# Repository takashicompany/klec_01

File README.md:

# KLEC-01 "Filled46"

https://x.com/takashicompany/status/1845085013051834711

# 部品リスト

|画像|部品名|個数|備考|
|:--|:--|:--|:--|
||KLEC-01 PCB|1|ガーバデータは[こちら](https://github.com/takashicompany/klec_01/tree/master/gerber)にあります。Kicadのプロジェクトは[こちら](https://github.com/takashicompany/klec_01/tree/master/kicad)です。|
||[Pro Micro](https://shop.yushakobo.jp/products/21)|1|どれを買っていいか分からない場合は[コンスルー付きのセット](https://shop.yushakobo.jp/products/21)の購入を推奨します。|
||[タクトスイッチ](https://shop.yushakobo.jp/products/a0800ts-01-1)|1||
||[コンスルー](https://shop.yushakobo.jp/products/31)|2|PCBとPro Microを接続する端子です。Pro Microに付属するピンヘッダでの取り付けも可能ですが、作業ミスや故障した際の取り替えが容易になりますので、**コンスルーの使用を強く推奨します。ピンヘッダでの取り付けは当キーボードと当ビルドガイドではサポートしません。** コンスルーの必要な高さはPro Microによって異なりますので、販売元にご確認ください。コンスルーについての詳細な説明は[こちら](https://scrapbox.io/self-made-kbds-ja/%E3%82%B3%E3%83%B3%E3%82%B9%E3%83%AB%E3%83%BC)をご一読ください。併せて[取り付け方の説明](https://yushakobo.zendesk.com/hc/ja/articles/360044233974-%E3%82%B3%E3%83%B3%E3%82%B9%E3%83%AB%E3%83%BC-%E3%82%B9%E3%83%97%E3%83%AA%E3%83%B3%E3%82%B0%E3%83%94%E3%83%B3%E3%83%98%E3%83%83%E3%83%80-%E3%81%AE%E5%8F%96%E3%82%8A%E4%BB%98%E3%81%91%E6%96%B9%E3%82%92%E6%95%99%E3%81%88%E3%81%A6%E4%B8%8B%E3%81%95%E3%81%84)も目を通しておくと作業がスムーズに進められます。|
||[MX互換キースイッチ](https://shop.yushakobo.jp/collections/all-switches)|46||
||[MX互換キーキャップ](https://shop.yushakobo.jp/collections/keycaps)|46|[こちら](https://www.keyboard-layout-editor.com/#/gists/d532e57cda0be36ffc0e33e7f8f69d8d)から各キーのサイズを確認できます。|
||[スタビライザー](https://shop.yushakobo.jp/products/a0500st)|2|
||[ウレタンクッション](https://shop.yushakobo.jp/products/a0800ur-01-6)|6|数はお好みで増減させてください。|
||アクリルケース|1|[こちらのデータ](https://github.com/takashicompany/klec_01/blob/master/case/klec_01_a4_yushakobo.ai)を遊舎工房の[レーザー加工サービス](https://shop.yushakobo.jp/products/lasercut?variant=48787700744423)にてカット依頼するなどして製造してください。後日に[キーボードアクリルプレート](https://shop.yushakobo.jp/products/keyboard_acrylic_plate)に追加予定です。|
||[M2スペーサー](https://shop.yushakobo.jp/products/a0800c2?variant=37665435222177)|8|長さはお好みで調整してください。Pro Microなどにもよりますが、7mm~10mmぐらいがオススメです。|
||[M2ネジ 5mm](https://shop.yushakobo.jp/products/a0800n2?variant=37665432993953)|16||

# ファームウェア

QMK Firmwareで用意しています。
ソースコードは[こちら](https://github.com/takashicompany/qmk_firmware/tree/master/keyboards/takashicompany/klec_01)です。

RemapにVIAファームウェアを登録しておりますので、[こちら](https://remap-keys.app/catalog/Tp7FO3o6xTwo2X9V9IJW/firmware)から書き込みが可能です。
キーマップの変更も[Remap](https://remap-keys.app/)から可能です。

# LICENSE

CC BY-NC 4.0

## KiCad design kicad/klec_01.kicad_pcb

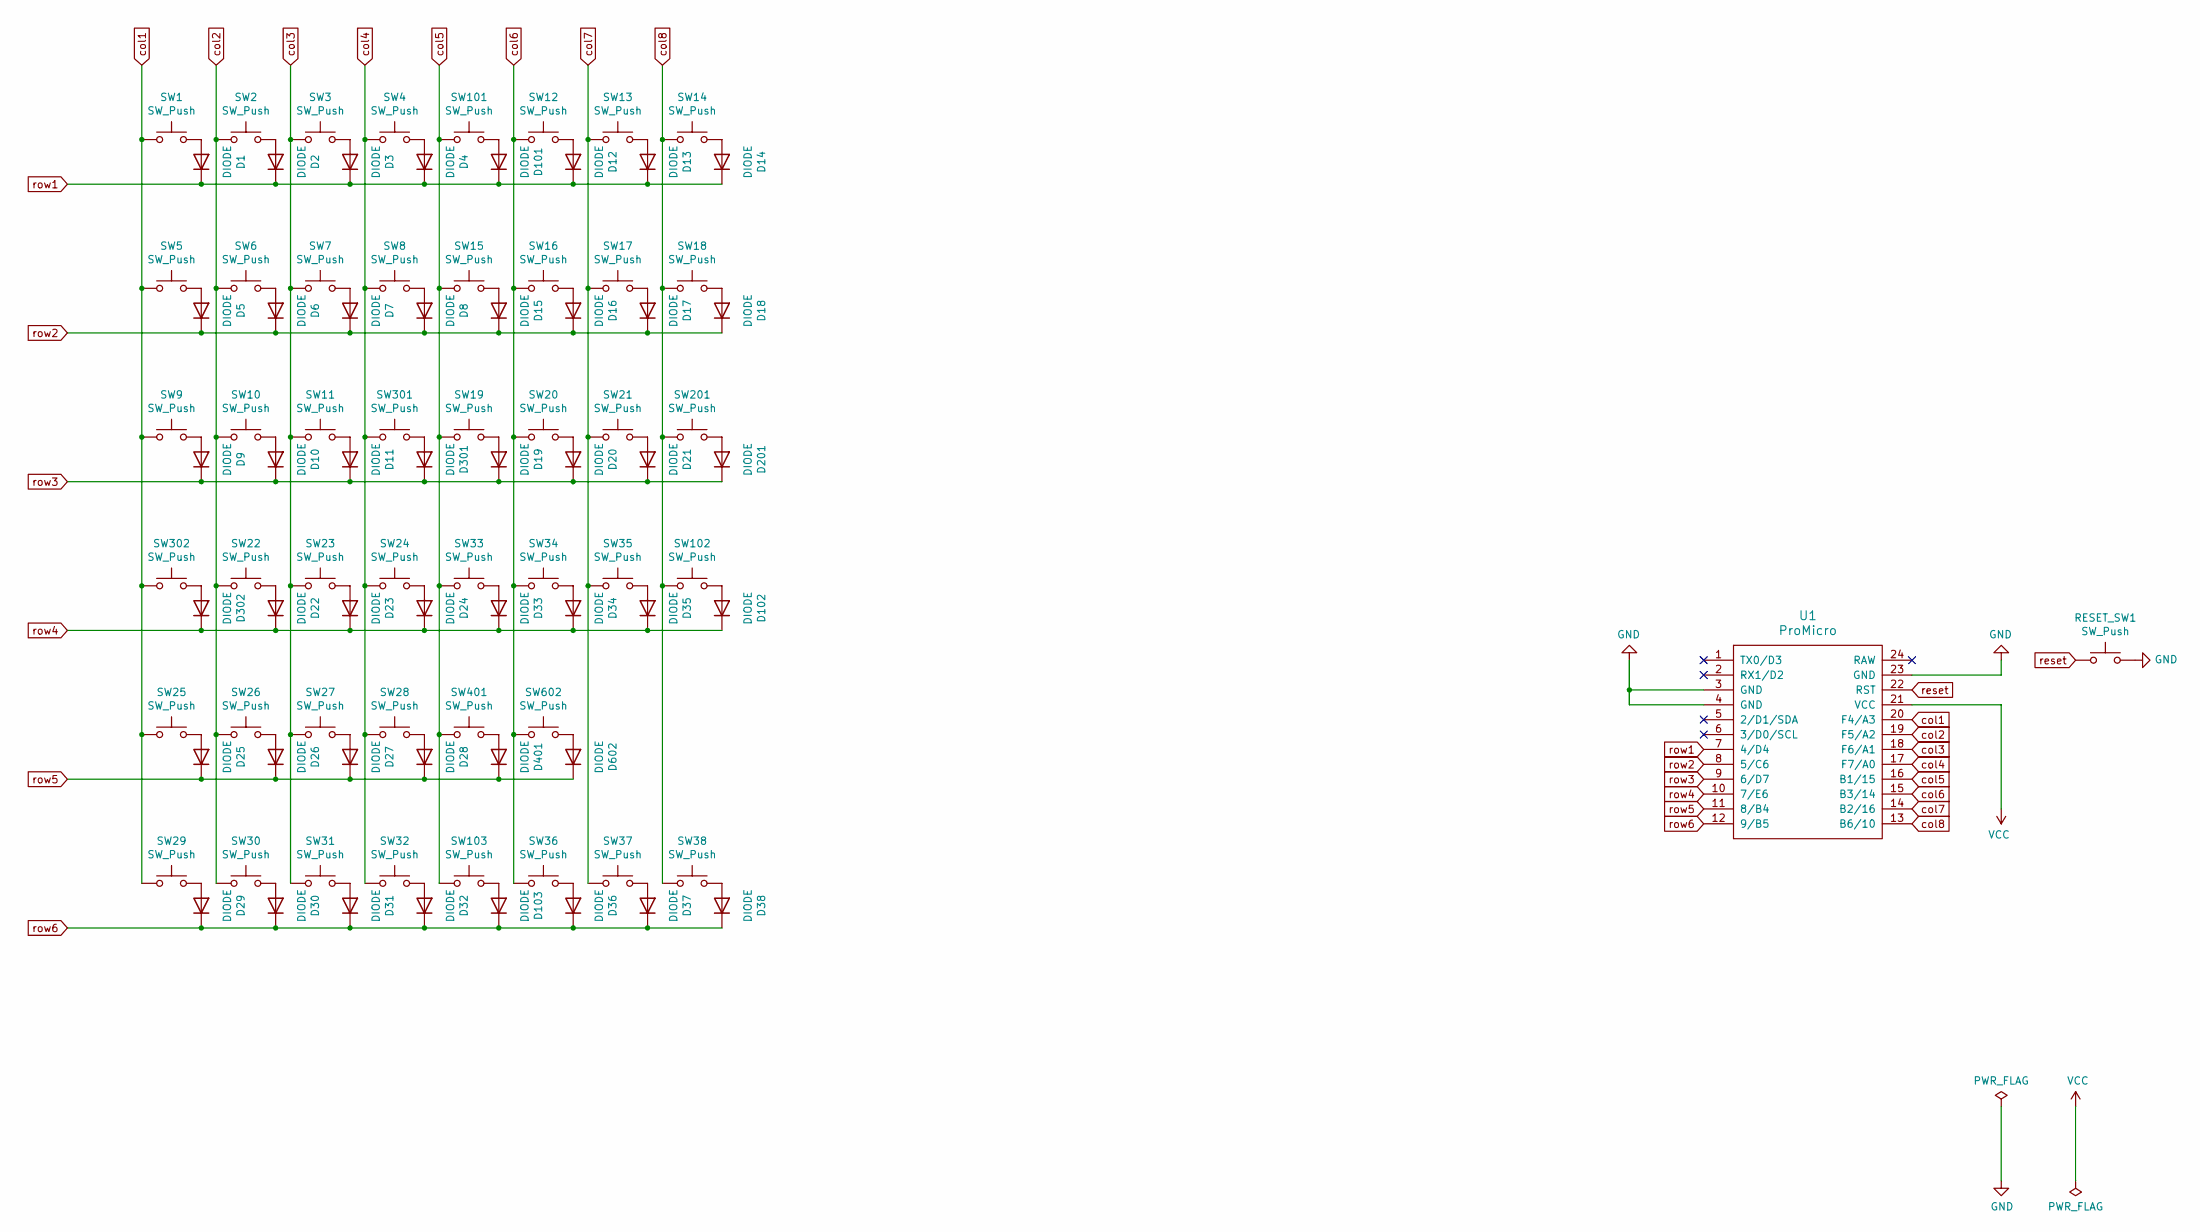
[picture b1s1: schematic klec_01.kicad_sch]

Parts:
D1, D2, D3, D4, D5, D6, D7, D8, D9, D10, D11, D12, D13, D14, D15, D16, D17, D18, D19, D20, D21, D22, D23, D24, D25, D26, D27, D28, D29, D30, D31, D32, D33, D34, D35, D36, D37, D38, D101, D102, D103, D201, D301, D302, D401, D602: DIODE; D3_TH_SMD_v2
RESET_SW1: SW_Push; ResetSW_1side
SW1, SW2, SW3, SW4, SW5, SW6, SW7, SW8, SW9, SW10, SW11, SW12, SW13, SW14, SW15, SW16, SW17, SW18, SW19, SW20, SW21, SW22, SW23, SW24, SW25, SW26, SW27, SW28, SW29, SW30, SW31, SW32, SW33, SW34, SW35, SW36, SW37, SW38: SW_Push; CherryMX_TH-Hotswap
SW101, SW102, SW103: SW_Push; CherryMX_TH-Hotswap_1.25u
SW201: SW_Push; CherryMX_TH-Hotswap_1.50u
SW301, SW302: SW_Push; CherryMX_TH-Hotswap_1.75u
SW401: SW_Push; CherryMX_TH-Hotswap_2.00u
SW602: SW_Push; CherryMX_TH-Hotswap_2.25u
U1: ProMicro; ProMicro_v3.5_print-inside_back

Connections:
GND: RESET_SW1.2, U1.3 (GND), U1.4 (GND), U1.23 (GND)
unnamed: D1.2 (A), SW1.2
unnamed: D2.2 (A), SW2.2
unnamed: D3.2 (A), SW3.2
unnamed: D4.2 (A), SW4.2
unnamed: D5.2 (A), SW5.2
unnamed: D6.2 (A), SW6.2
unnamed: D7.2 (A), SW7.2
unnamed: D8.2 (A), SW8.2
unnamed: D9.2 (A), SW9.2
unnamed: D10.2 (A), SW10.2
unnamed: D11.2 (A), SW11.2
unnamed: D12.2 (A), SW12.2
unnamed: D13.2 (A), SW13.2
unnamed: D14.2 (A), SW14.2
unnamed: D15.2 (A), SW15.2
unnamed: D16.2 (A), SW16.2
unnamed: D17.2 (A), SW17.2
unnamed: D18.2 (A), SW18.2
unnamed: D19.2 (A), SW19.2
unnamed: D20.2 (A), SW20.2
unnamed: D21.2 (A), SW21.2
unnamed: D22.2 (A), SW22.2
unnamed: D23.2 (A), SW23.2
unnamed: D24.2 (A), SW24.2
unnamed: D25.2 (A), SW25.2
unnamed: D26.2 (A), SW26.2
unnamed: D27.2 (A), SW27.2
unnamed: D28.2 (A), SW28.2
unnamed: D29.2 (A), SW29.2
unnamed: D30.2 (A), SW30.2
unnamed: D31.2 (A), SW31.2
unnamed: D32.2 (A), SW32.2
unnamed: D33.2 (A), SW33.2
unnamed: D34.2 (A), SW34.2
unnamed: D35.2 (A), SW35.2
unnamed: D36.2 (A), SW36.2
unnamed: D37.2 (A), SW37.2
unnamed: D38.2 (A), SW38.2
unnamed: D101.2 (A), SW101.2
unnamed: D102.2 (A), SW102.2
unnamed: D103.2 (A), SW103.2
unnamed: D201.2 (A), SW201.2
unnamed: D301.2 (A), SW301.2
unnamed: D302.2 (A), SW302.2
unnamed: D401.2 (A), SW401.2
unnamed: D602.2 (A), SW602.2
VCC: U1.21 (VCC)
col1: SW1.1, SW5.1, SW9.1, SW25.1, SW29.1, SW302.1, U1.20 (F4/A3)
col2: SW2.1, SW6.1, SW10.1, SW22.1, SW26.1, SW30.1, U1.19 (F5/A2)
col3: SW3.1, SW7.1, SW11.1, SW23.1, SW27.1, SW31.1, U1.18 (F6/A1)
col4: SW4.1, SW8.1, SW24.1, SW28.1, SW32.1, SW301.1, U1.17 (F7/A0)
col5: SW15.1, SW19.1, SW33.1, SW101.1, SW103.1, SW401.1, U1.16 (B1/15)
col6: SW12.1, SW16.1, SW20.1, SW34.1, SW36.1, SW602.1, U1.15 (B3/14)
col7: SW13.1, SW17.1, SW21.1, SW35.1, SW37.1, U1.14 (B2/16)
col8: SW14.1, SW18.1, SW38.1, SW102.1, SW201.1, U1.13 (B6/10)
reset: RESET_SW1.1, U1.22 (RST)
row1: D1.1 (K), D2.1 (K), D3.1 (K), D4.1 (K), D12.1 (K), D13.1 (K), D14.1 (K), D101.1 (K), U1.7 (4/D4)
row2: D5.1 (K), D6.1 (K), D7.1 (K), D8.1 (K), D15.1 (K), D16.1 (K), D17.1 (K), D18.1 (K), U1.8 (5/C6)
row3: D9.1 (K), D10.1 (K), D11.1 (K), D19.1 (K), D20.1 (K), D21.1 (K), D201.1 (K), D301.1 (K), U1.9 (6/D7)
row4: D22.1 (K), D23.1 (K), D24.1 (K), D33.1 (K), D34.1 (K), D35.1 (K), D102.1 (K), D302.1 (K), U1.10 (7/E6)
row5: D25.1 (K), D26.1 (K), D27.1 (K), D28.1 (K), D401.1 (K), D602.1 (K), U1.11 (8/B4)
row6: D29.1 (K), D30.1 (K), D31.1 (K), D32.1 (K), D36.1 (K), D37.1 (K), D38.1 (K), D103.1 (K), U1.12 (9/B5)

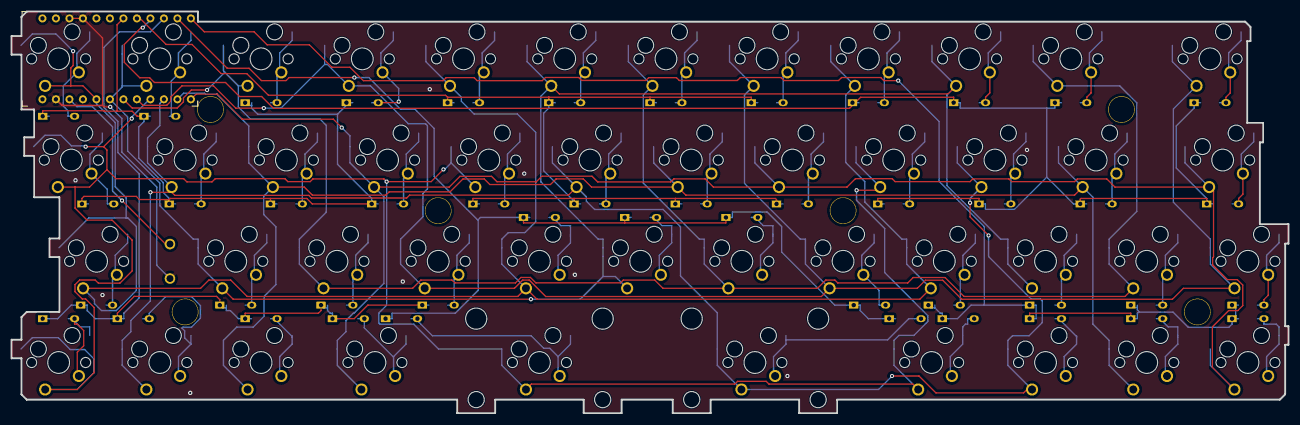
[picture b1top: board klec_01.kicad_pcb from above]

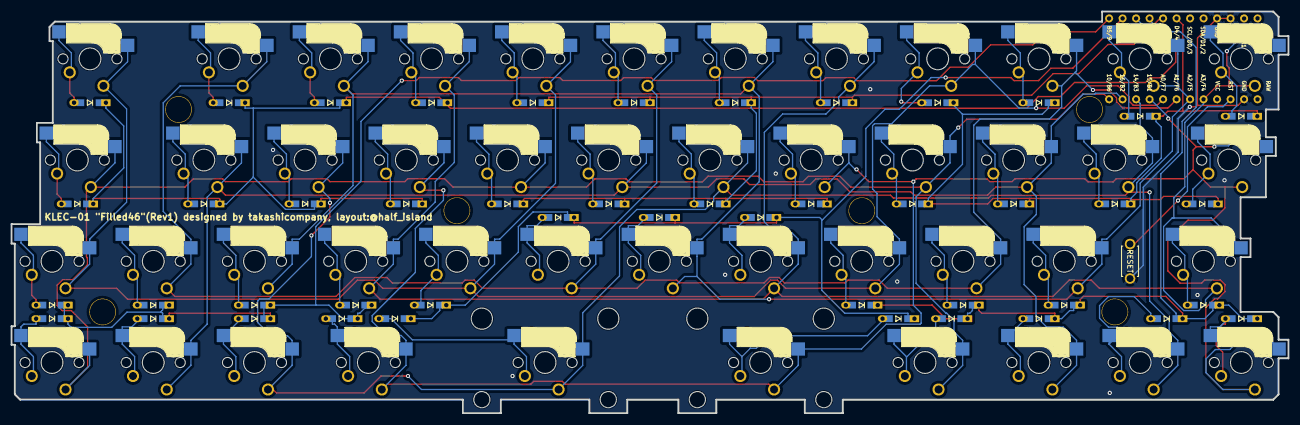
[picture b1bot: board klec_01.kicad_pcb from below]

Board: 2 copper layers, 240.3 x 75.6 mm, 102 parts (47 on the bottom side), 62 nets.

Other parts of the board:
Hole01, Hole02, Hole03, Hole04, Hole05, Hole06: Val**; HOLE
Stab01, Stab02: Stabilizer_MX_2u

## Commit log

2024-10-13 gerbar and kicad
2024-10-13 Create LICENSE
2024-10-13 Update LICENSE
2024-11-04 ケースデータ
